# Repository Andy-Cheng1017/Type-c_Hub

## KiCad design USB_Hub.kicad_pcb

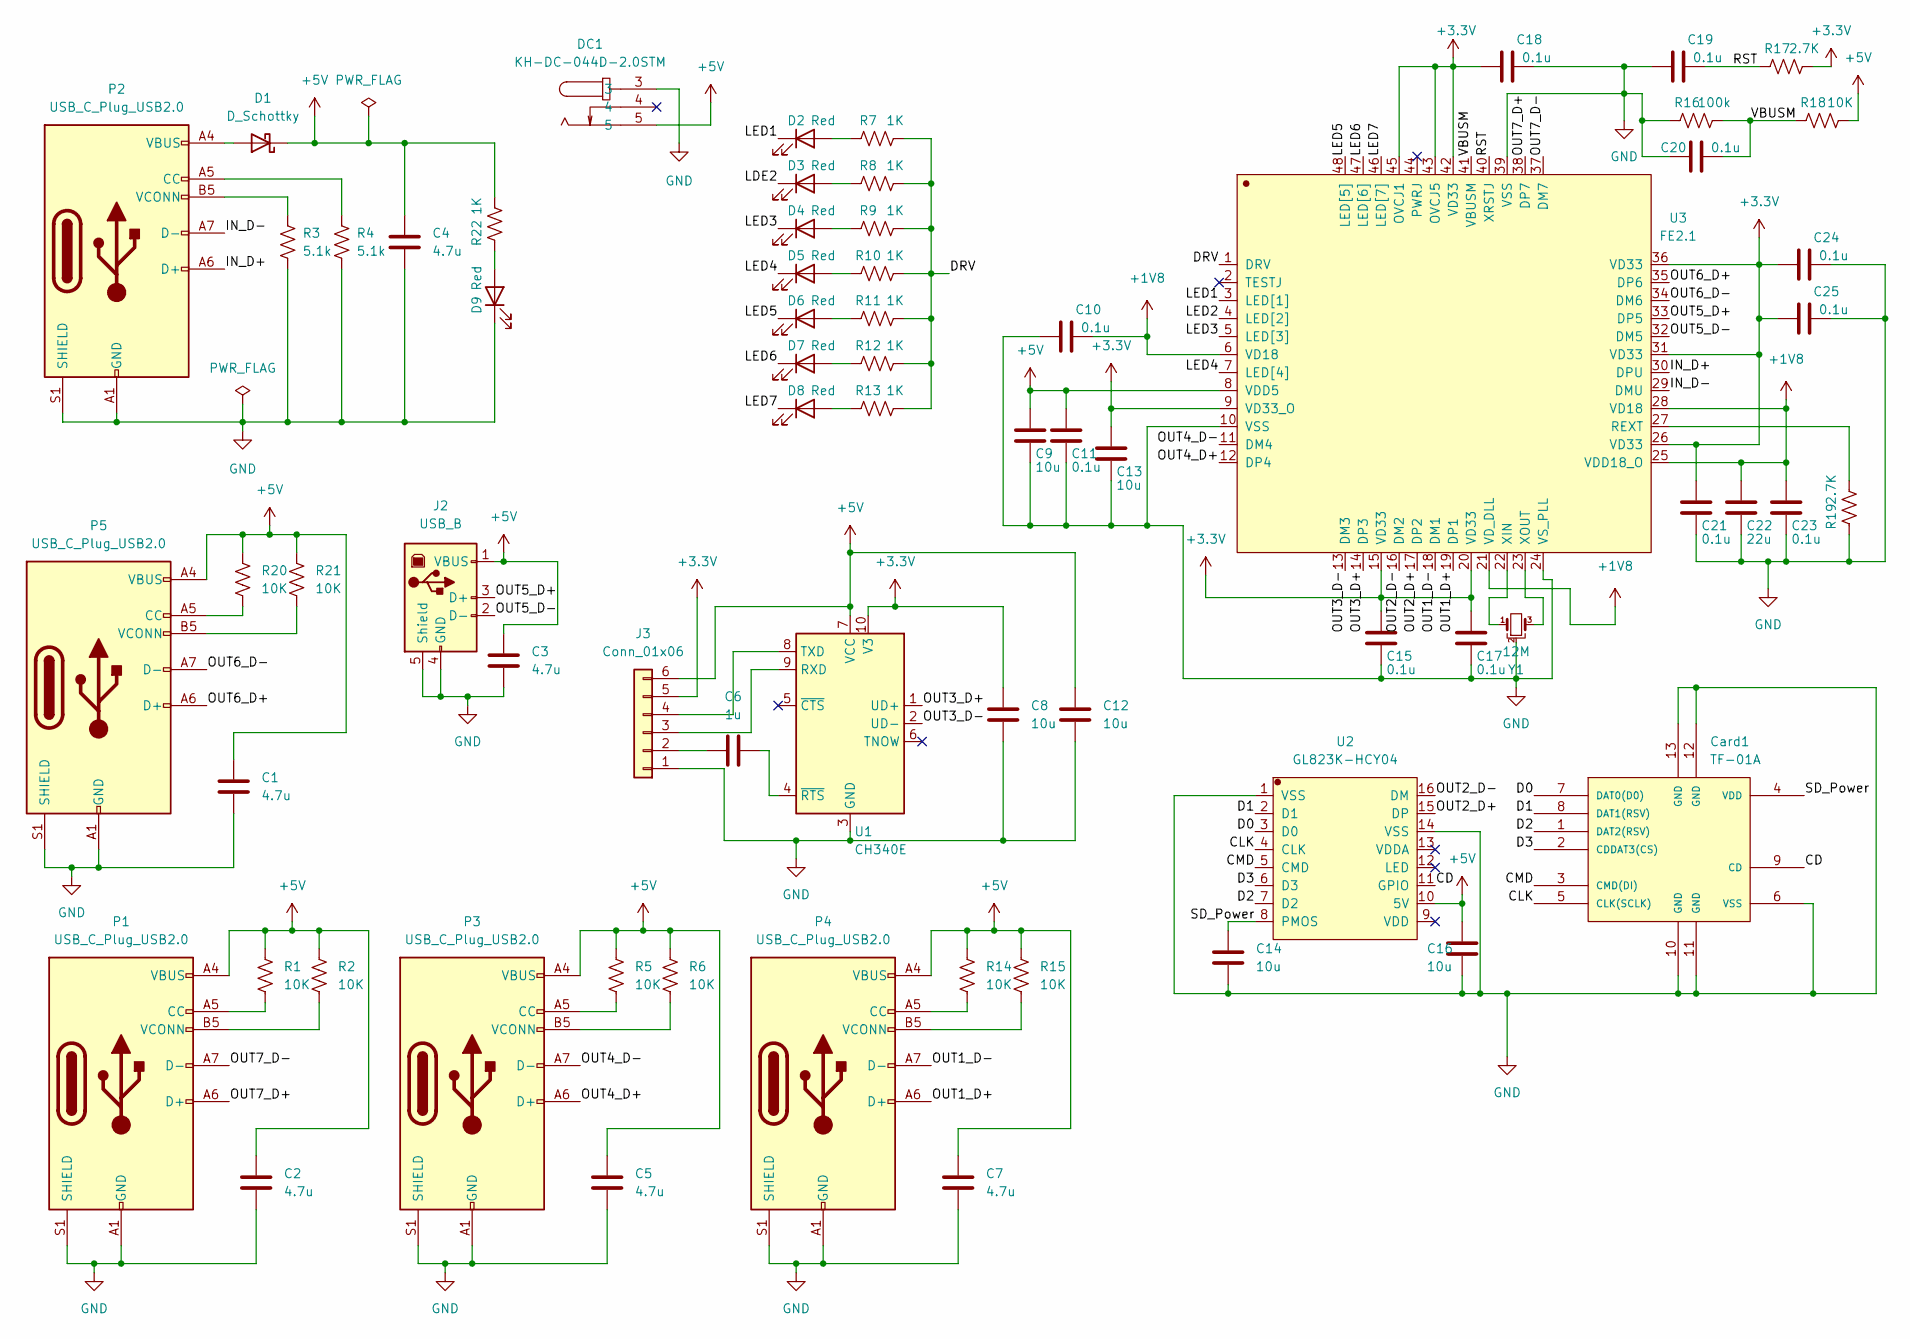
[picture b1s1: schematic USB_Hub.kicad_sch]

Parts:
C1, C2, C3, C4, C5, C7: 4.7u; C_0805_2012Metric
C6: 1u; C_0805_2012Metric
C8, C9, C12, C13, C14, C16: 10u; C_0805_2012Metric
C10, C11, C15, C17, C18, C19, C20, C21, C23, C24, C25: 0.1u; C_0805_2012Metric
C22: 22u; C_0805_2012Metric
Card1: TF-01A; TF-SMD_TF-01A
D1: D_Schottky; D_SMA
D2, D3, D4, D5, D6, D7, D8, D9: Red; LED_0805_2012Metric
DC1: KH-DC-044D-2.0STM; DC-IN-TH_KH-DC-044D-2.0STM
J2: USB_B; USB-A-TH_C42425
J3: Conn_01x06; PinHeader_1x06_P2.54mm_Horizontal
P1, P3, P4, P5: USB_C_Plug_USB2.0; USB-C-SMD_TYPEC-303-ACP16
P2: USB_C_Plug_USB2.0; USB_C_Receptacle_HRO_TYPE-C-31-M-12
R1, R2, R5, R6, R14, R15, R18, R20, R21: 10K; R_0805_2012Metric
R3, R4: 5.1k; R_0805_2012Metric
R7, R8, R9, R10, R11, R12, R13, R22: 1K; R_0805_2012Metric
R16: 100k; R_0805_2012Metric
R17, R19: 2.7K; R_0805_2012Metric
U1: CH340E; MSOP-10_3x3mm_P0.5mm
U2: GL823K-HCY04; SSOP-16_3.9x4.9mm_P0.635mm
U3: FE2.1; LQFP-48_7x7mm_P0.5mm
Y1: 12M; Resonator_SMD_Murata_CSTxExxV-3Pin_3.0x1.1mm

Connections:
+1V8: C10.2, C22.1, C23.1, U3.6 (VD18), U3.21 (VD_DLL), U3.25 (VDD18_O), U3.28 (VD18)
+3.3V: C8.1, C13.1, C15.1, C17.1, C18.1, C21.1, C24.1, C25.1, J3.5, R17.1, U1.10 (V3), U3.9 (VD33_O), U3.15 (VD33), U3.20 (VD33), U3.26 (VD33), U3.31 (VD33), U3.36 (VD33), U3.42 (VD33), U3.43 (OVCJ5), U3.45 (OVCJ1)
+5V: C1.1, C2.1, C3.1, C4.1, C5.1, C7.1, C9.1, C11.1, C12.1, C16.1, D1.1 (K), DC1.5, J2.1 (VBUS), J3.6, P1.A4 (VBUS), P1.A9 (VBUS), P1.B4 (VBUS), P1.B9 (VBUS), P3.A4 (VBUS), P3.A9 (VBUS), P3.B4 (VBUS), P3.B9 (VBUS), P4.A4 (VBUS), P4.A9 (VBUS), P4.B4 (VBUS), P4.B9 (VBUS), P5.A4 (VBUS), P5.A9 (VBUS), P5.B4 (VBUS), P5.B9 (VBUS), R1.1, R2.1, R5.1, R6.1, R14.1, R15.1, R18.1, R20.1, R21.1, R22.1, U1.7 (VCC), U2.10 (5V), U3.8 (VDD5)
/CD: Card1.9 (CD), U2.11 (GPIO)
/CLK: Card1.5 (CLK(SCLK)), U2.4 (CLK)
/CMD: Card1.3 (CMD(DI)), U2.5 (CMD)
/D0: Card1.7 (DAT0(D0)), U2.3 (D0)
/D1: Card1.8 (DAT1(RSV)), U2.2 (D1)
/D2: Card1.1 (DAT2(RSV)), U2.7 (D2)
/D3: Card1.2 (CDDAT3(CS)), U2.6 (D3)
/DRV: R7.1, R8.1, R9.1, R10.1, R11.1, R12.1, R13.1, U3.1 (DRV)
/IN_D+: P2.A6 (D+), U3.30 (DPU)
/IN_D-: P2.A7 (D-), U3.29 (DMU)
/LDE2: D3.1 (K)
/LED1: D2.1 (K), U3.3 (LED[1])
/LED2: U3.4 (LED[2])
/LED3: D4.1 (K), U3.5 (LED[3])
/LED4: D5.1 (K), U3.7 (LED[4])
/LED5: D6.1 (K), U3.48 (LED[5])
/LED6: D7.1 (K), U3.47 (LED[6])
/LED7: D8.1 (K), U3.46 (LED[7])
/OUT1_D+: P4.A6 (D+), U3.19 (DP1)
/OUT1_D-: P4.A7 (D-), U3.18 (DM1)
/OUT2_D+: U2.15 (DP), U3.17 (DP2)
/OUT2_D-: U2.16 (DM), U3.16 (DM2)
/OUT3_D+: U1.1 (UD+), U3.14 (DP3)
/OUT3_D-: U1.2 (UD-), U3.13 (DM3)
/OUT4_D+: P3.A6 (D+), U3.12 (DP4)
/OUT4_D-: P3.A7 (D-), U3.11 (DM4)
/OUT5_D+: J2.3 (D+), U3.33 (DP5)
/OUT5_D-: J2.2 (D-), U3.32 (DM5)
/OUT6_D+: P5.A6 (D+), U3.35 (DP6)
/OUT6_D-: P5.A7 (D-), U3.34 (DM6)
/OUT7_D+: P1.A6 (D+), U3.38 (DP7)
/OUT7_D-: P1.A7 (D-), U3.37 (DM7)
/RST: C19.2, R17.2, U3.40 (XRSTJ)
/SD_Power: C14.1, Card1.4 (VDD), U2.8 (PMOS)
/VBUSM: C20.2, R16.1, R18.2, U3.41 (VBUSM)
GND: C1.2, C2.2, C3.2, C4.2, C5.2, C7.2, C8.2, C9.2, C10.1, C11.2, C12.2, C13.2, C14.2, C15.2, C16.2, C17.2, C18.2, C19.1, C20.1, C21.2, C22.2, C23.2, C24.2, C25.2, Card1.6 (VSS), Card1.10 (GND), Card1.11 (GND), Card1.12 (GND), Card1.13 (GND), D9.1 (K), DC1.3, J2.4 (GND), J2.5 (Shield), J3.1, P1.A1 (GND), P1.A12 (GND), P1.B1 (GND), P1.B12 (GND), P1.S1 (SHIELD), P2.A1 (GND), P2.A12 (GND), P2.B1 (GND), P2.B12 (GND), P2.S1 (SHIELD), P3.A1 (GND), P3.A12 (GND), P3.B1 (GND), P3.B12 (GND), P3.S1 (SHIELD), P4.A1 (GND), P4.A12 (GND), P4.B1 (GND), P4.B12 (GND), P4.S1 (SHIELD), P5.A1 (GND), P5.A12 (GND), P5.B1 (GND), P5.B12 (GND), P5.S1 (SHIELD), R3.2, R4.2, R16.2, R19.2, U1.3 (GND), U2.1 (VSS), U2.14 (VSS), U3.10 (VSS), U3.24 (VS_PLL), U3.39 (VSS), Y1.2
unnamed: C6.1, U1.4 (~RTS)
unnamed: C6.2, J3.2
unnamed: D1.2 (A), P2.A4 (VBUS), P2.A9 (VBUS), P2.B4 (VBUS), P2.B9 (VBUS)
unnamed: D2.2 (A), R7.2
unnamed: D3.2 (A), R8.2
unnamed: D4.2 (A), R9.2
unnamed: D5.2 (A), R10.2
unnamed: D6.2 (A), R11.2
unnamed: D7.2 (A), R12.2
unnamed: D8.2 (A), R13.2
unnamed: D9.2 (A), R22.2
unnamed: J3.3, U1.9 (RXD)
unnamed: J3.4, U1.8 (TXD)
unnamed: P1.A5 (CC), R1.2
unnamed: P1.B5 (VCONN), R2.2
unnamed: P2.A5 (CC), R4.1
unnamed: P2.B5 (VCONN), R3.1
unnamed: P3.A5 (CC), R5.2
unnamed: P3.B5 (VCONN), R6.2
unnamed: P4.A5 (CC), R14.2
unnamed: P4.B5 (VCONN), R15.2
unnamed: P5.A5 (CC), R20.2
unnamed: P5.B5 (VCONN), R21.2
unnamed: R19.1, U3.27 (REXT)
unnamed: U3.22 (XIN), Y1.1
unnamed: U3.23 (XOUT), Y1.3

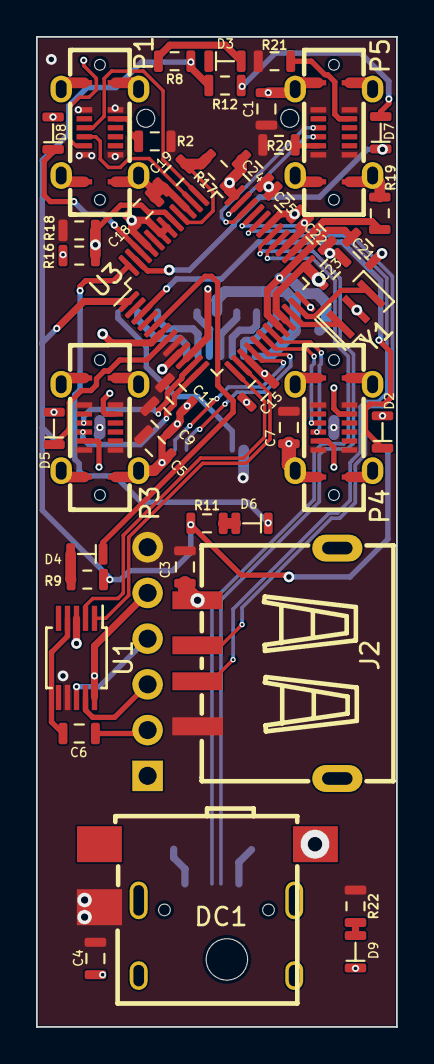
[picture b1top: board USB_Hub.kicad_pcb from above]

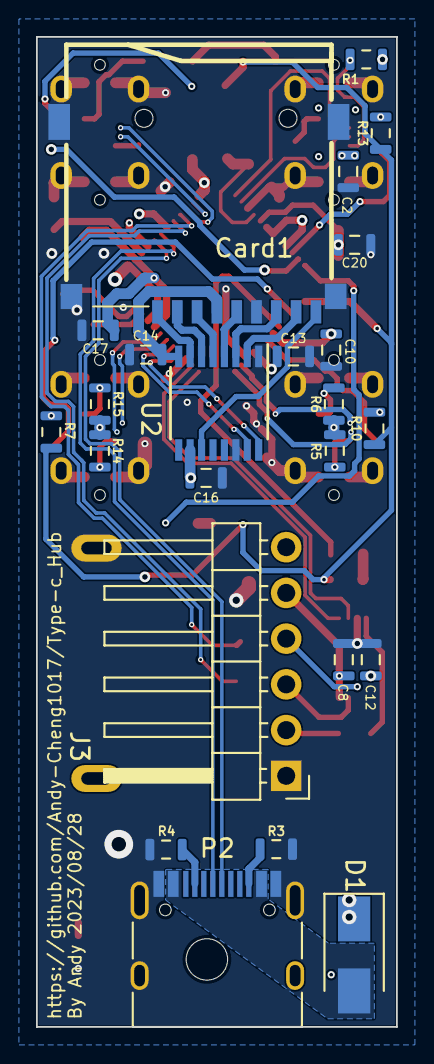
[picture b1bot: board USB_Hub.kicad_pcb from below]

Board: 4 copper layers, 20.0 x 55.0 mm, 69 parts (24 on the bottom side), 63 nets.

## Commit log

2023-08-05 高鐵更新
2023-11-06 test
